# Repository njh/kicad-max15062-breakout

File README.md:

MAX15062 Breakout
=================

This KiCad project provides an open-source breakout board for the [MAX15062](https://www.analog.com/en/products/max15062.html) high-efficiency, high-voltage, synchronous step-down DC-DC converter IC. The board is designed to deliver up to **300mA at 3.3V** from input voltages as high as 60V.

Schematic 
---------

PCB Layout
----------

KiCad Version
-------------

Created with **KiCad 9.0.1**

License
-------

This project is licensed under the [MIT License](LICENSE.md).

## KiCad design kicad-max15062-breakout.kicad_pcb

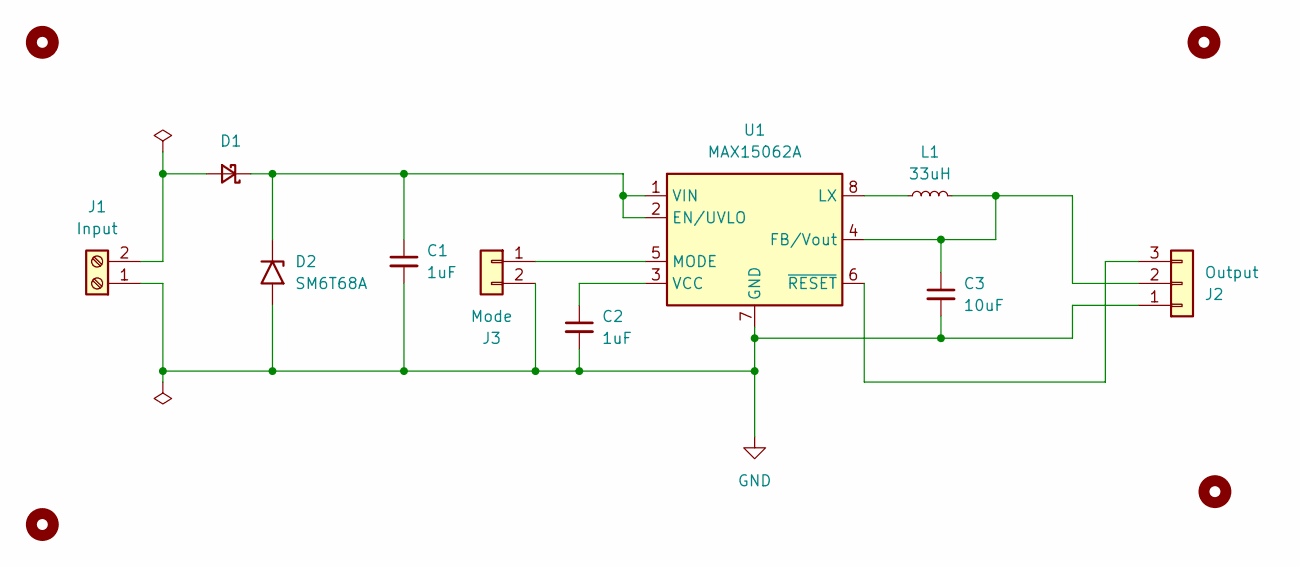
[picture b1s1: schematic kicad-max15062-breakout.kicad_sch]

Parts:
C1, C2: 1uF; C_1206_3216Metric; LCSC C70463
C3: 10uF; C_0805_2012Metric; LCSC C15850
D1: D_Schottky_Small; D_SMA; LCSC C14996
D2: SM6T68A; D_SMB; LCSC C133686
H1, H2, H3, H4: MountingHole; MountingHole_2.2mm_M2
J1: Input; PhoenixContact_MCV_1,5_2-G-3.5_1x02_P3.50mm_Vertical
J2: Output; PinHeader_1x03_P2.54mm_Vertical
J3: Mode; PinHeader_1x02_P2.54mm_Vertical
L1: 33uH; L_1812_4532Metric; LCSC C394127
U1: MAX15062A; DFN-8_2x2mm_P0.5mm; LCSC C2846801

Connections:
GND: C1.2, C2.2, C3.2, D2.2 (A2), J1.1, J2.1, J3.2, U1.7 (GND)
unnamed: D1.2 (A), J1.2
unnamed: C1.1, D1.1 (K), D2.1 (A1), U1.1 (VIN), U1.2 (EN/UVLO)
unnamed: C3.1, J2.2, L1.2, U1.4 (FB/Vout)
unnamed: J2.3, U1.6 (~RESET)
unnamed: J3.1, U1.5 (MODE)
unnamed: L1.1, U1.8 (LX)
unnamed: C2.1, U1.3 (VCC)

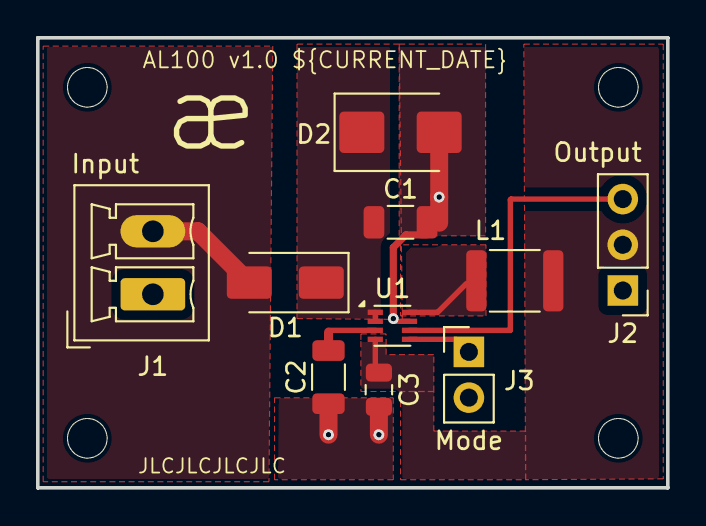
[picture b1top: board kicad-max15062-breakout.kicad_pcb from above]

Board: 2 copper layers, 35.0 x 25.0 mm, 14 parts (0 on the bottom side), 8 nets.

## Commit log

2025-06-29 Added first version of Schematic and PCB
2025-06-29 Added gitignore
2025-06-29 Added README and LICENSE
2025-07-01 Added autosave and jlcpcb to gitignore
2025-07-01 Added mounting holes to the schematic
2025-07-01 Removed through-hole components from the BOM
2025-07-01 Added LCSC (JLCPCB) part numbers to the schematic parts
2025-07-06 Improved PCB layout and added text to silkscreen
2025-07-06 Added images to README
